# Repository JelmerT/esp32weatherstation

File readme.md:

### This repository holds the firmware for a weather station based on the ESP32.

Original firmware and hardware were published in Elektor magazine: https://www.elektormagazine.com/magazine/elektor-70/42351  
Design by Roy Aarts.

The changes in this repo from the original design:  
- Removed SDS011 PM sensor and replaced by PMS5003

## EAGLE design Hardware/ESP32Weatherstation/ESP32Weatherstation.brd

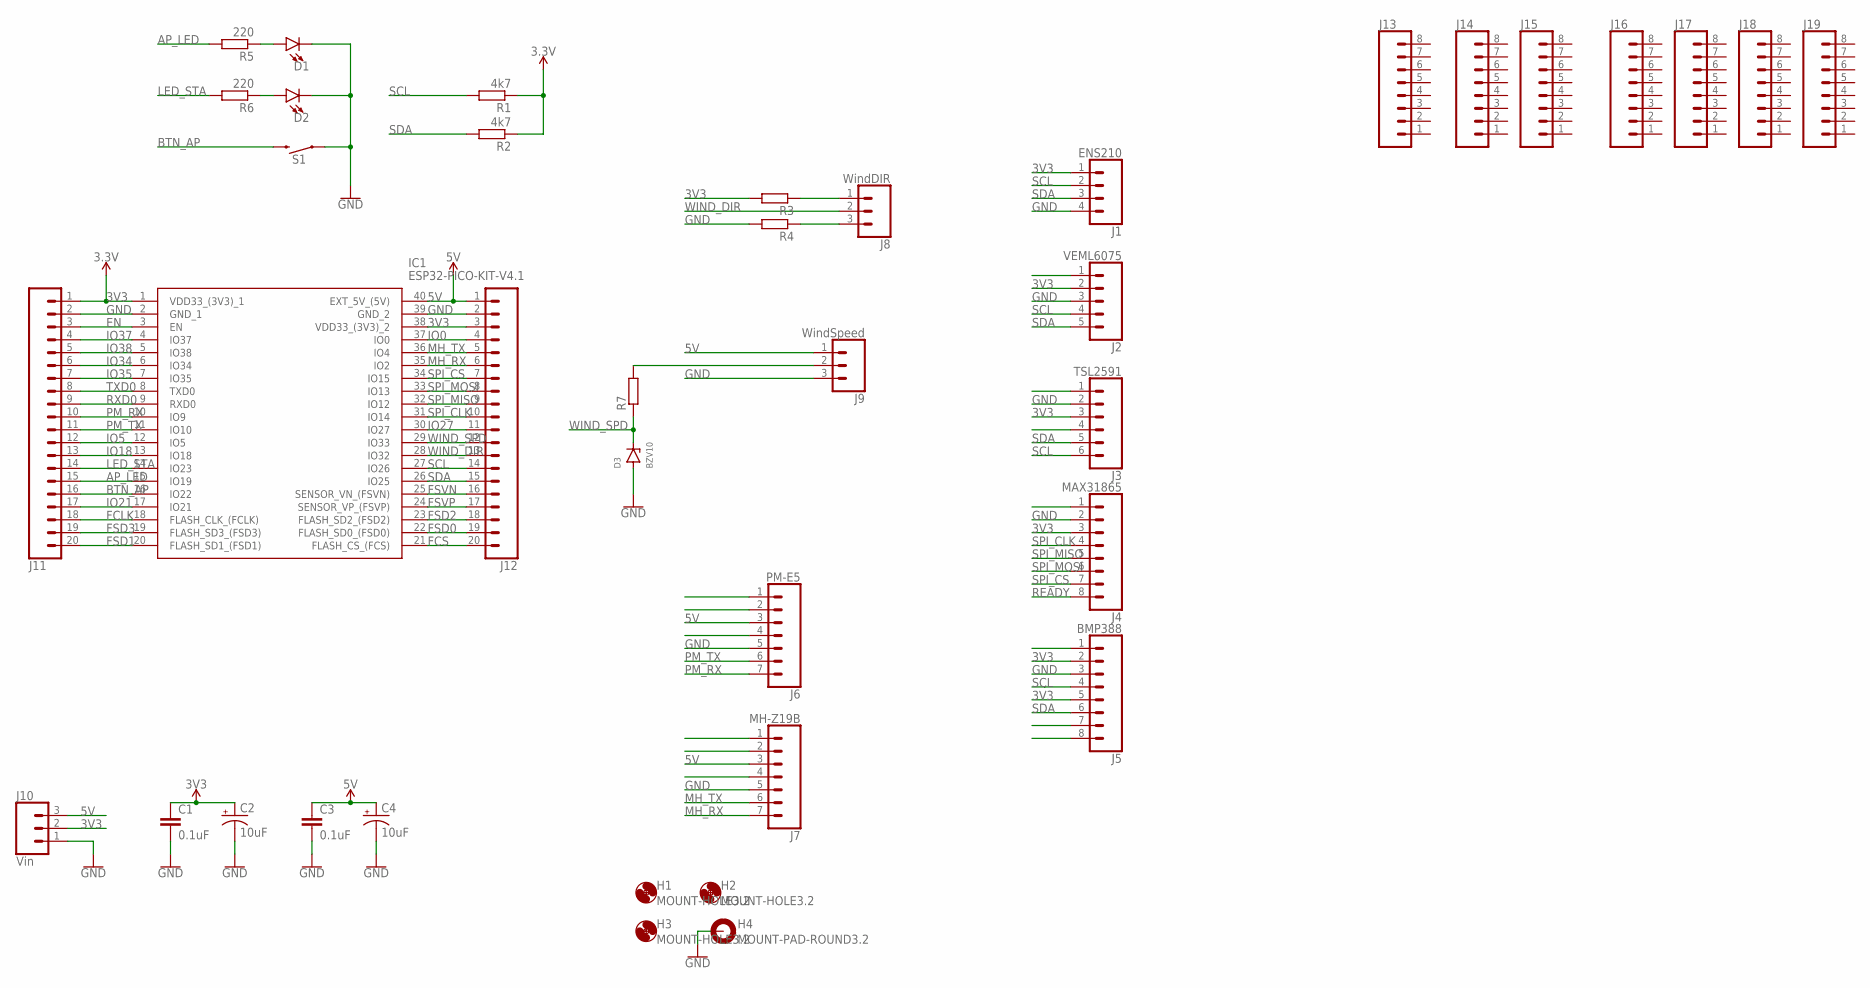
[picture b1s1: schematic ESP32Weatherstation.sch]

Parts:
C1, C3: 0.1uF; 0603
C2, C4: 10uF; EIA3216
D1, D2: LED3MM; LED_3MM
D3: BZV10; DO34Z7
H1, H2, H3: MOUNT-HOLE3.2; 3,2
H4: MOUNT-PAD-ROUND3.2; 3,2-PAD
IC1: ESP32-PICO-KIT-V4.1; DIPS1778W60P254L5200H1300Q40N
J1: ENS210; 1X04_NO_SILK
J2: VEML6075; 1X05_NO_SILK
J3: TSL2591; 1X06_NO_SILK
J4: MAX31865; 1X08_NO_SILK
J5: BMP388; 1X08_NO_SILK
J6: PM-E5; 1X07_NO_SILK
J7: MH-Z19B; 1X07_NO_SILK
J8: WindDIR; 1X03_NO_SILK
J9: WindSpeed; 1X03_NO_SILK
J10: Vin; 1X03_NO_SILK
J11, J12: CONN_20NOSILK; 1X20_NOSILK
J13, J14, J15, J16, J17, J18, J19: CONN_08NO_SILK_FEMALE_PTH; 1X08_NO_SILK
R1, R2: 4k7; 0207/10
R3, R4, R7: R-EU_0207/10; 0207/10
R5, R6: 220; 0207/10
S1: MOMENTARY-SWITCH-SPST-SMD-5.2MM; TACTILE_SWITCH_SMD_5.2MM

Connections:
3V3: C1.1, C2.+, IC1.1 (VDD33_(3V3)_1), IC1.38 (VDD33_(3V3)_2), J1.1, J2.2, J3.3, J4.3, J5.2, J5.5, J10.2, J11.1, J12.3, R1.1, R2.1, R3.2
5V: C3.1, C4.+, IC1.40 (EXT_5V_(5V)), J6.3, J7.3, J9.1, J10.3, J12.1
AP_LED: IC1.15 (IO19), J11.15, R5.2
BTN_AP: IC1.16 (IO22), J11.16, S1.3 (2)
EN: IC1.3 (EN), J11.3
FCLK: IC1.18 (FLASH_CLK_(FCLK)), J11.18
FCS: IC1.21 (FLASH_CS_(FCS)), J12.20
FSD0: IC1.22 (FLASH_SD0_(FSD0)), J12.19
FSD1: IC1.20 (FLASH_SD1_(FSD1)), J11.20
FSD2: IC1.23 (FLASH_SD2_(FSD2)), J12.18
FSD3: IC1.19 (FLASH_SD3_(FSD3)), J11.19
FSVN: IC1.25 (SENSOR_VN_(FSVN)), J12.16
FSVP: IC1.24 (SENSOR_VP_(FSVP)), J12.17
GND: C1.2, C2.-, C3.2, C4.-, D1.K (C), D2.K (C), D3.A, H4.B3,2, IC1.2 (GND_1), IC1.39 (GND_2), J1.4, J2.3, J3.2, J4.2, J5.3, J6.5, J7.5, J9.3, J10.1, J11.2, J12.2, R4.2, S1.1
IO0: IC1.37 (IO0), J12.4
IO5: IC1.12 (IO5), J11.12
IO18: IC1.13 (IO18), J11.13
IO21: IC1.17 (IO21), J11.17
IO27: IC1.30 (IO27), J12.11
IO34: IC1.6 (IO34), J11.6
IO35: IC1.7 (IO35), J11.7
IO37: IC1.4 (IO37), J11.4
IO38: IC1.5 (IO38), J11.5
LED_STA: IC1.14 (IO23), J11.14, R6.2
MH_RX: IC1.35 (IO2), J7.7, J12.6
MH_TX: IC1.36 (IO4), J7.6, J12.5
unnamed: J8.1, R3.1
unnamed: D1.A, R5.1
unnamed: D2.A, R6.1
unnamed: J8.3, R4.1
unnamed: J9.2, R7.2
PM_RX: IC1.10 (IO9), J6.7, J11.10
PM_TX: IC1.11 (IO10), J6.6, J11.11
READY: J4.8
RXD0: IC1.9 (RXD0), J11.9
SCL: IC1.27 (IO26), J1.2, J2.4, J3.6, J5.4, J12.14, R1.2
SDA: IC1.26 (IO25), J1.3, J2.5, J3.5, J5.6, J12.15, R2.2
SPI_CLK: IC1.31 (IO14), J4.4, J12.10
SPI_CS: IC1.34 (IO15), J4.7, J12.7
SPI_MISO: IC1.32 (IO12), J4.5, J12.9
SPI_MOSI: IC1.33 (IO13), J4.6, J12.8
TXD0: IC1.8 (TXD0), J11.8
WIND_DIR: IC1.28 (IO32), J8.2, J12.13
WIND_SPD: D3.C, IC1.29 (IO33), J12.12, R7.1

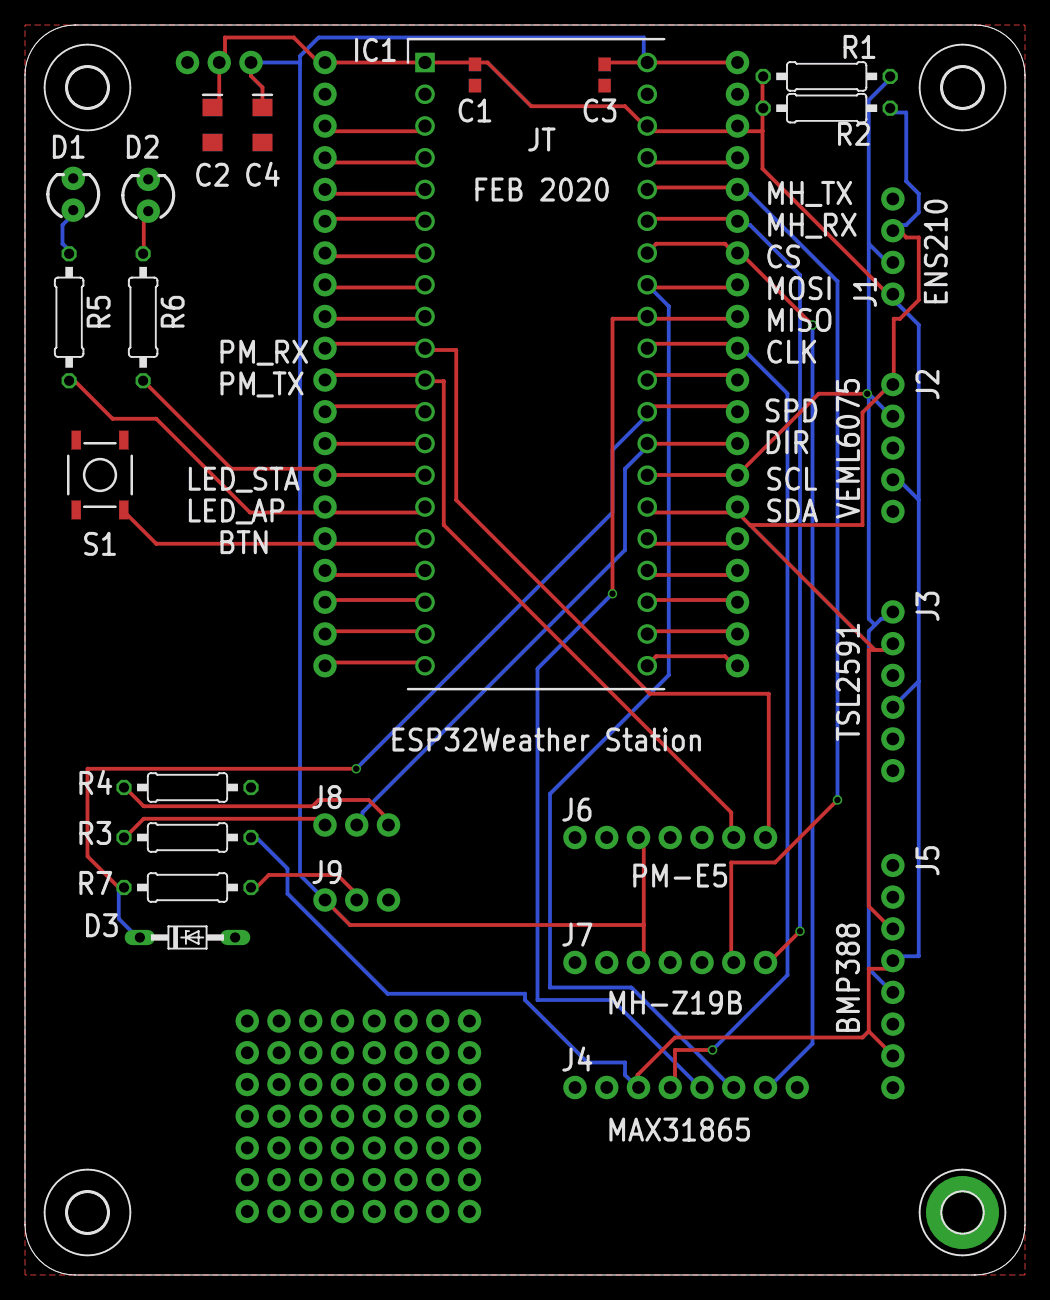
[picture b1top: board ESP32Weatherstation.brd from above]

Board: 2 copper layers, 80.0 x 100.0 mm, 39 parts (0 on the bottom side), 43 nets.

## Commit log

2019-05-31 removed sds011
2019-05-31 more removing sds011
2019-06-04 added wind direction in degrees
2019-06-06 added bmp388 tsl2591 veml6075
2019-06-06 cleanup
2019-06-06 added max31865
2019-06-16 enabled webserver during client mode. Added upload to ubidots
2019-06-18 updated gitignore
2020-02-05 added ENS210 and MHZ19
2020-02-05 added ENS210 lib
2020-02-10 updated file structure, added new sensors, added custom PCB design
2020-03-20 added missing lib
2020-03-21 added param VEML6075 & security
2020-03-29 Work in progress
2020-03-29 fixed missing brackets
2020-03-29 add stripped down, serial only, firmware
2020-03-29 add comments
2020-04-07 add serial echo
2020-04-08 improve serial input, configure project to use miniterm.py
2020-04-12 intermediate save
2020-04-12 move all prints to print function, remove some var that werent used, add seperate print interval, improve measurement function
2020-04-13 cleaning up txt
2020-04-13 cleaning up txt further
2020-04-19 Work in progress, blinky
2020-04-19 add time library, clean up blink functions
2020-05-05 Hall sensor test
2020-05-05 add rainsensorRead via esp internal hall sensor. Remove old rainSensor external class
2020-05-05 improve rain sensor init
2020-06-11 add RTC proto
2020-06-12 add RV-3028-C7 example
2020-06-12 removed old firmware
2020-06-18 removed arduino time lib
2020-06-18 add `weather meters` library for wind dir, speed and rain
2020-06-18 removed old wind libs
2020-06-18 improved platform.ini
2020-06-18 fix weather lib implementation
2020-06-18 add rtc time sync with compile time
2020-06-19 testing with WeatherStation
2020-06-19 added local copy of weathermeters
2020-06-19 enabled debugging on weather lib
2020-06-19 add pinmode for weather lib and fix interrupts
2020-06-21 convert weather lib to continues resistor value wind dir
2020-06-21 temp fix interrupt issue
2020-06-21 more windvane fixes

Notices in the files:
parts and their libraries:
SparkFun-Connectors: Licensing: Creative Commons ShareAlike 4.0 International - https://creativecommons.org/licenses/by-sa/4.0
